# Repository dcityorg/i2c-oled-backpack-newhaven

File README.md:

#### I²C OLED Backpack Board for the Newhaven OLED displays

<div style="text-align: center;">
<div style="display: inline-block; margin-right: 5px;">

</div>

<div style="display: inline-block; margin-right: 5px;">

</div>

<div style="display: inline-block; margin-right: 5px;">

</div>
</div>

**[This link has details](https://www.dcity.org/portfolio/i2c-oled-backpack-board-newhaven) including**
* parts lists
* assembly instructions
* jumper configuration
* Arduino, Particle and Raspberry Pi software library usage
* Bare PC boards are available from OSHPark.

**License Information**
Open Source Hardware Design. Our License Information is [here](https://www.dcity.org/license-information/).

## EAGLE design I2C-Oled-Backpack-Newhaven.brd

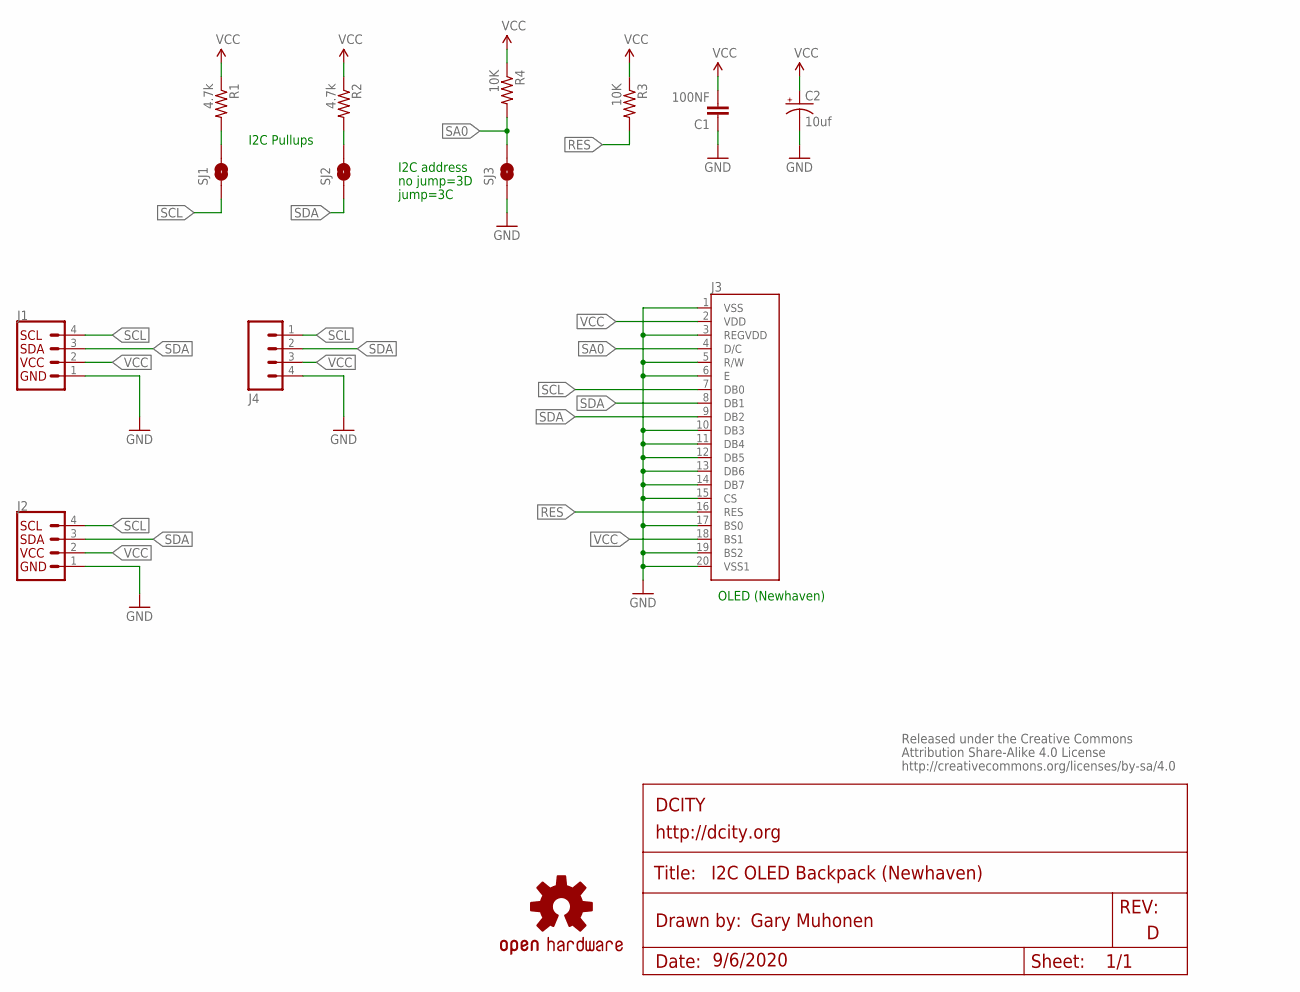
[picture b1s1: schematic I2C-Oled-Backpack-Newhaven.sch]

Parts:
C1: 100NF; 0805-CAP
C2: 10uf; 0805-POL
J1, J2: QWIIC_RIGHT_ANGLE; JST04_1MM_RA
J3: LCD-NEWHAVEN-LOCK; 1X20_LOCK
J4: M04LOCK; 1X04_LOCK
LOGO1: OSHW-LOGOS; OSHW-LOGO-S
R1, R2: 4.7k; 0805-RES
R3, R4: 10K; 0805-RES
SJ1, SJ2, SJ3: SOLDERJUMPERNC; SJ_2S
U$2: CREATIVE_COMMONS

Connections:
GND: C1.1, C2.-, J1.1, J2.1, J3.1 (VSS), J3.3 (REGVDD), J3.5 (R/W), J3.6 (E), J3.10 (DB3), J3.11 (DB4), J3.12 (DB5), J3.13 (DB6), J3.14 (DB7), J3.15 (CS), J3.17 (BS0), J3.19 (BS2), J3.20 (VSS1), J4.4, SJ3.1
unnamed: R1.2, SJ1.2
unnamed: R2.2, SJ2.2
RES: J3.16 (RES), R3.2
SA0: J3.4 (D/C), R4.2, SJ3.2
SCL: J1.4, J2.4, J3.7 (DB0), J4.1, SJ1.1
SDA: J1.3, J2.3, J3.8 (DB1), J3.9 (DB2), J4.2, SJ2.1
VCC: C1.2, C2.+, J1.2, J2.2, J3.2 (VDD), J3.18 (BS1), J4.3, R1.1, R2.1, R3.1, R4.1

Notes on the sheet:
I2C address
no jump=3D
jump=3C
I2C Pullups
OLED (Newhaven)

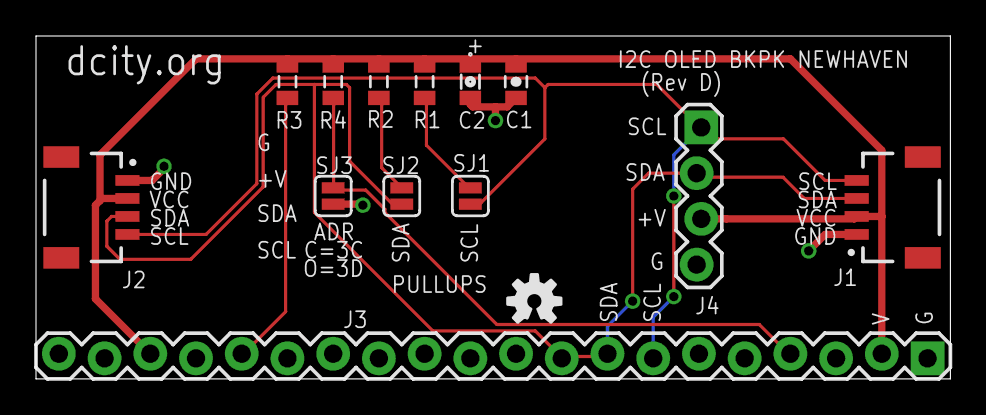
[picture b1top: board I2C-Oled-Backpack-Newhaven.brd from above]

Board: 2 copper layers, 50.8 x 19.1 mm, 15 parts (0 on the bottom side), 8 nets.

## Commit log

2016-04-05 First commit - Rev A
2016-04-08 Rev B design
2016-04-13 changed pictures in readme.md
2016-04-13 minor change to readme.md
2018-09-14 Rev C
2020-10-08 Rev D
2020-10-08 Rev D pictures
2020-10-08 Rev D pictures correction
2020-10-11 update pictures

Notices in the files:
parts and their libraries:
0: Released under the Creative Commons
0: http://creativecommons.org/licenses/by-sa/4.0
